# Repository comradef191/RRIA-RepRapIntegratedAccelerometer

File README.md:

# Duet3D-Accelerometer
A standalone accelerometer board using the LIS3DH(v0.2) or LIS2DW12(v1.0) MEMS digital motion sensor. It is designed to plug into the SPI daughterboard header on Duet 2 and 3 mainboards.

Product Page:
[https://www.duet3d.com/duet3d-accelerometer](https://www.duet3d.com/duet3d-accelerometer)

Documentation is here:

[Duet 3 Accelerometer Documentation](https://docs.duet3d.com/en/Duet3D_hardware/Accessories/Duet3D_Accelerometer)

licensed under the "CERN-OHL-S v2" or any later version plus the "Additional Duet3D Licence Terms",
see https://github.com/Duet3D/Duet3-Mainboard-6HC/blob/master/LICENSE

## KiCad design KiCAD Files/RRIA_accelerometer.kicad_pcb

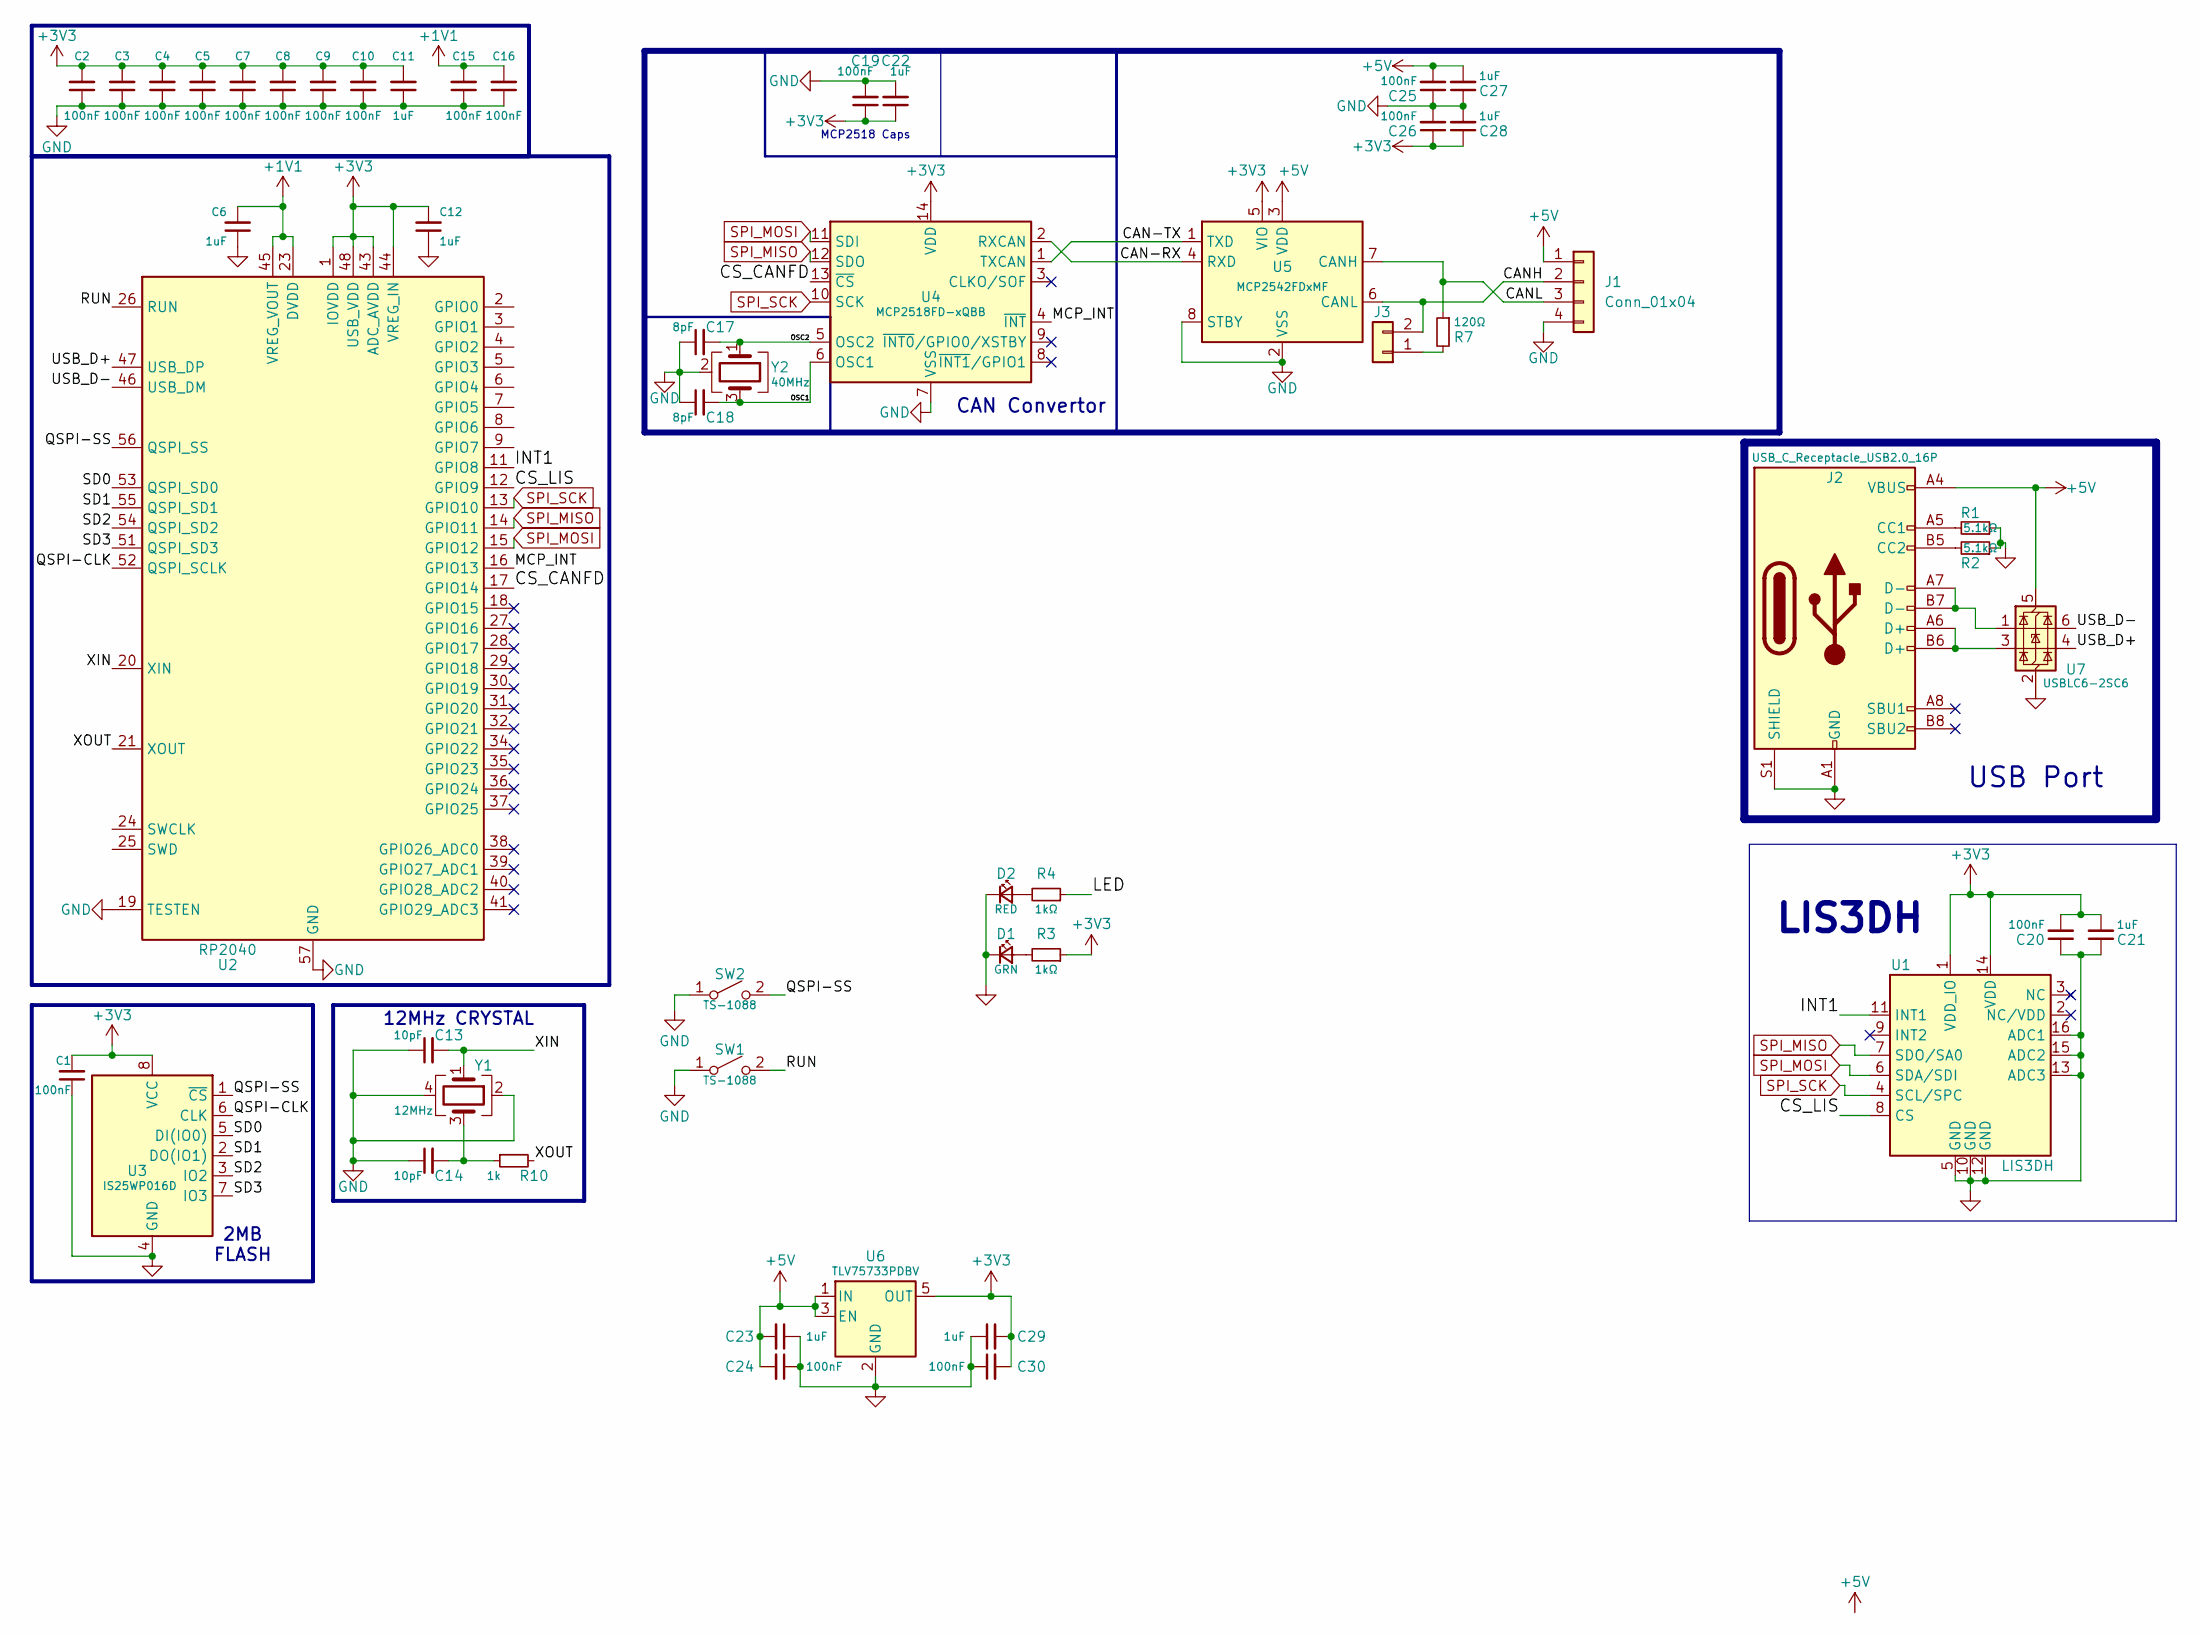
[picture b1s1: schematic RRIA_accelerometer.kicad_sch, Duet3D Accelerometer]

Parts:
C1, C2, C3, C4, C5, C7, C8, C9, C10, C15, C16: 100nF; C_0402_1005Metric
C6, C11, C12: 1uF; C_0402_1005Metric
C13, C14: 10pF; C_0402_1005Metric
C17, C18: 8pF; C_0402_1005Metric
C19, C20, C25, C26: 100nF; C_0402_1005Metric; LCSC C541464
C21, C22, C27, C28: 1uF; C_0402_1005Metric; LCSC C2887020
C23, C29: 1uF; C_0402_1005Metric; LCSC C52923
C24, C30: 100nF; C_0402_1005Metric; LCSC C1525
D1: GRN; LED_0805_2012Metric; LCSC C2297
D2: RED; LED_0805_2012Metric; LCSC C84256
J1: Conn_01x04; JST_XH_S4B-XH-A_1x04_P2.50mm_Horizontal
J2: USB_C_Receptacle_USB2.0_16P; USB_C_Receptacle_HRO_TYPE-C-31-M-12; LCSC C165948
J3: 2.54-Header-1x2; PinHeader_1x02_P2.54mm_Vertical
R1, R2: 5.1kΩ; R_0402_1005Metric; LCSC C25905
R3, R4: 1kΩ; R_0402_1005Metric; LCSC C11702
R7: 120Ω; R_0402_1005Metric; LCSC C25079
R10: 1k; R_0402_1005Metric
SW1, SW2: TS-1088; SW_SPST_TS-1088-xR025; LCSC C720477
U1: LIS3DH; LGA-16_3x3mm_P0.5mm_LISD3H; Part Number LIS3DHTR
U2: RP2040; QFN-56-1EP_7x7mm_P0.4mm_EP3.2x3.2mm_ThermalVias
U3: IS25WP016D; Winbond_USON-8-1EP_3x2mm_P0.5mm_EP0.2x1.6mm; LCSC C2976734
U4: MCP2518FD-xQBB; DFN-14-1EP_3x4.5mm_P0.65mm_EP1.65x4.25mm; LCSC C621395
U5: MCP2542FDxMF; DFN-8-1EP_3x3mm_P0.65mm_EP1.7x2.05mm; LCSC C635109
U6: TLV75733PDBV; SOT-23-5; LCSC C485517
U7: USBLC6-2SC6; SOT-23-6; LCSC C7519
Y1: 12MHz; Crystal_SMD_2520-4Pin_2.5x2.0mm; LCSC C7294610
Y2: 40MHz

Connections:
+1V1: C6.2, C15.2, C16.2, U2.23 (DVDD), U2.45 (VREG_VOUT), U2.50 (DVDD)
+3V3: C1.2, C2.2, C3.2, C4.2, C5.2, C7.2, C8.2, C9.2, C10.2, C11.2, C12.2, C19.1, C20.2, C21.2, C22.1, C26.1, C28.1, C29.2, C30.2, R3.1, U1.1 (VDD_IO), U1.14 (VDD), U2.1 (IOVDD), U2.10 (IOVDD), U2.22 (IOVDD), U2.33 (IOVDD), U2.42 (IOVDD), U2.43 (ADC_AVDD), U2.44 (VREG_IN), U2.48 (USB_VDD), U2.49 (IOVDD), U3.8 (VCC), U4.14 (VDD), U5.5 (VIO), U6.5 (OUT)
+5V: C23.2, C24.2, C25.2, C27.2, J1.1, J2.A4 (VBUS), J2.A9 (VBUS), J2.B4 (VBUS), J2.B9 (VBUS), U5.3 (VDD), U6.1 (IN), U6.3 (EN), U7.5 (VBUS)
/CAN-RX: U4.2 (RXCAN), U5.4 (RXD)
/CAN-TX: U4.1 (TXCAN), U5.1 (TXD)
/CANH: J1.2, J3.2, U5.6 (CANL)
/CANL: J1.3, R7.1, U5.7 (CANH)
/CS_CANFD: U2.17 (GPIO14), U4.13 (~CS)
/CS_LIS: U1.8 (CS), U2.12 (GPIO9)
/INT1: U1.11 (INT1), U2.11 (GPIO8)
/LED: R4.1
/MCP_INT: U2.16 (GPIO13), U4.4 (~INT)
/OSC1: C18.2, U4.6 (OSC1), Y2.3
/OSC2: C17.2, U4.5 (OSC2), Y2.1
/QSPI-CLK: U2.52 (QSPI_SCLK), U3.6 (CLK)
/QSPI-SS: SW2.2 (B), U2.56 (QSPI_SS), U3.1 (~CS)
/RUN: SW1.2 (B), U2.26 (RUN)
/SD0: U2.53 (QSPI_SD0), U3.5 (DI(IO0))
/SD1: U2.55 (QSPI_SD1), U3.2 (DO(IO1))
/SD2: U2.54 (QSPI_SD2), U3.3 (IO2)
/SD3: U2.51 (QSPI_SD3), U3.7 (IO3)
/USB_D+: U2.47 (USB_DP), U7.4 (I/O2)
/USB_D-: U2.46 (USB_DM), U7.6 (I/O1)
/XIN: C13.2, U2.20 (XIN), Y1.1
/XOUT: R10.2, U2.21 (XOUT)
GND: C1.1, C2.1, C3.1, C4.1, C5.1, C6.1, C7.1, C8.1, C9.1, C10.1, C11.1, C12.1, C13.1, C14.1, C15.1, C16.1, C17.1, C18.1, C19.2, C20.1, C21.1, C22.2, C23.1, C24.1, C25.1, C26.2, C27.1, C28.2, C29.1, C30.1, D1.1 (K), D2.1 (K), J1.4, J2.A1 (GND), J2.A12 (GND), J2.B1 (GND), J2.B12 (GND), J2.S1 (SHIELD), R1.1, R2.1, SW1.1 (A), SW2.1 (A), U1.5 (GND), U1.10 (GND), U1.12 (GND), U1.13 (ADC3), U1.15 (ADC2), U1.16 (ADC1), U2.19 (TESTEN), U2.57 (GND), U3.4 (GND), U3.9 (GND), U4.7 (VSS), U4.15 (VSS), U5.2 (VSS), U5.8 (STBY), U5.9 (VSS), U6.2 (GND), U7.2 (GND), Y1.2, Y1.4, Y2.2 (G), Y2.4 (G)
unnamed: C14.2, R10.1, Y1.3
unnamed: D1.2 (A), R3.2
unnamed: D2.2 (A), R4.2
unnamed: J2.A5 (CC1), R1.2
unnamed: J2.B5 (CC2), R2.2
unnamed: J2.A6 (D+), J2.B6 (D+), U7.3 (I/O2)
unnamed: J2.A7 (D-), J2.B7 (D-), U7.1 (I/O1)
unnamed: J3.1, R7.2
SPI_MISO: U1.7 (SDO/SA0), U2.14 (GPIO11), U4.12 (SDO)
SPI_MOSI: U1.6 (SDA/SDI), U2.15 (GPIO12), U4.11 (SDI)
SPI_SCK: U1.4 (SCL/SPC), U2.13 (GPIO10), U4.10 (SCK)

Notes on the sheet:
12MHz CRYSTAL
CAN Convertor
MCP2518 Caps
USB Port
2MB FLASH
LIS3DH

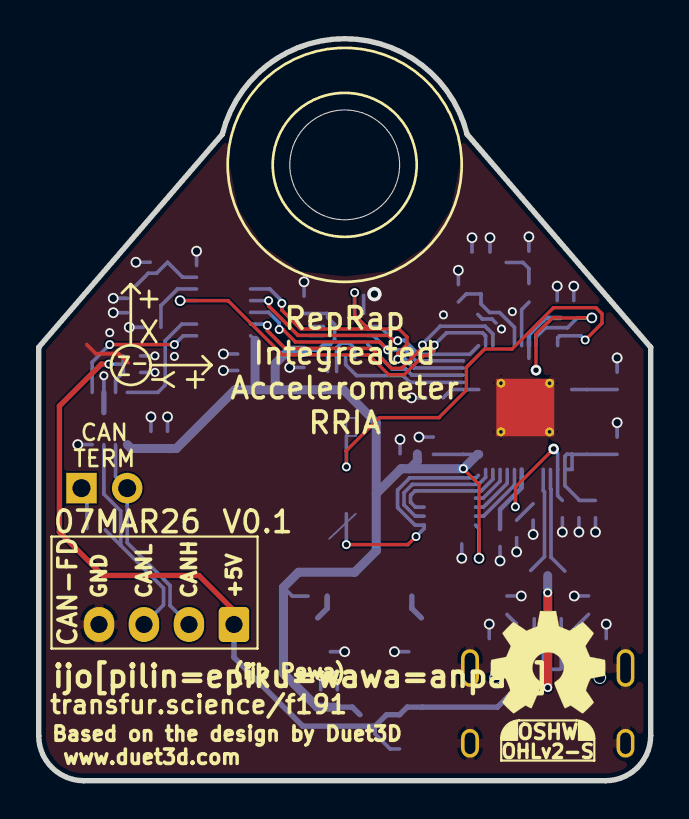
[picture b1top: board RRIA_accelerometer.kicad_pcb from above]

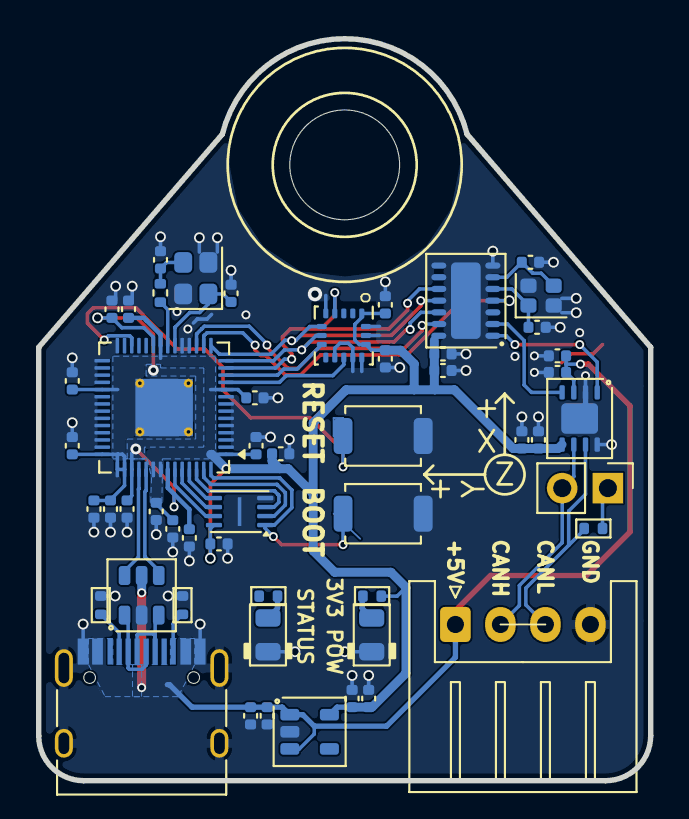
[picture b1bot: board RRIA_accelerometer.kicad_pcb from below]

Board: 2 copper layers, 34.0 x 41.2 mm, 53 parts (52 on the bottom side), 36 nets.

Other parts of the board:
H1: M6; MountingHole_6mm

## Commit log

2026-04-04 Rename files; Prep
2026-04-04 gitignore + prep for RP2040
2026-04-05 progress
2026-05-09 Final
